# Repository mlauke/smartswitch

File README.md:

# Sonnen SmartSwitch
DIY sonnen battery controller based on ESP8266/ESP32 to drive a 3.3kW heater (Heißwasserspeicher-Einbauheizung) and integrates with the local hot water system.

## Features
- accesses the local hot water system (boiler system) via **LPB** to get the hot water system data - e.g. hot water temparature
- calculate battery capacity and surplus from **solar forecast** to optimize the self consumption
- local web interface to customize system parameters

## UI

## Software / Releases
the software supports ESP8266 and ESP32 modules, which can be build for the appropriate target platform. releases can be found at https://github.com/mlauke/smartswitch/releases/

### Build
Install uv (https://docs.astral.sh/uv/concepts/tools/) and run proceed to source folder
```bash
cd smartswitch.espxx
# run tests
uv run pio test -e native
# run build
uv run pio run -e esp32 -e esp8266
# run check for outdated packages
uv run pio pkg outdated
```

## Hardware
the reference implementation (at my home) uses the following components
- Heater - https://www.austria-email.at/produkte/zubehoer/elektro-einbauheizung/reu-18-33/
- Hot Water Tank - https://www.austria-email.at/produkte/indirekt-beheizte-speicher/standspeicher/standspeicher-hr/hr-160/
- Sonnen Battery https://sonnen.de/stromspeicher/sonnenbatterie-10/
- Boiler System - Siemens RVD250 attached and connected to the ESP controller via the Local Process Bus (LPB)
- ESP8266/ESP32 controller modules
- ArduiBox housing https://www.az-delivery.de/en/products/arduibox-nodemcu-hutschienen-montage-und-anschluss-set
- DIN Rail Power supply +12V
- AC mains Triac cicuit to drive a 1NO Relay
- 1NO Relay (Schütz) https://www.reichelt.de/de/de/shop/produkt/schaltrelais_1_s_230_v_ac_16_a-155592

### Schematics

The schematics and pcb is drawn with KiCad. The pcb uses a special layout which exactly matches the usable part of the ArduiBox's circuit board. KiCad files can be found <a href="kicad/">here.</a>

<p align="center">

</p>

### Housing

<details open align="center">
<summary>Housing</summary>

<!--a href="public/sss_fusebox_big.png">

</details>

### Thoughts
#### Why not using a TRIAC only solution?
Although Triacs have very low Rs_on values in nowadays, they become very hot depending on the load to drive. Using a 3.3kW heater will require a big heatsink as can be seen in the calculation below.

```bash
Pmax = (Tj,max - Tamb,max) / Rth

I = P / U = 3300W / 230 V = 14,35A
Rs_on (BTA25) = 0,16 Ohm
P_loss = U * I = Rs_on * I * I
P_loss = 0,16 Ohm * (14,35 A)²
P_loss = 32,95W

R_max = (T_max - T_env) / P_loss
R_max = (120°C - 40°C) / 33W
R_max = 2,42K/W
R_heatsink = R_max - R_jc = 2,42K/W - 1,7K/W
R_heatsink = 0,7K/W !!!
```

... heatsink with <=0,7K/W makes no sense, because we will waste too much power wasted just for heating the environment and maybe would "blow up" the overall system design in terms of size and housing the components.
therefore i decided to use a triac as switching device for a simple NO1 relais ("Schütz") which in turn will drive the load. the NO1 relais can directly placed next to the arduino case on our din rail.

#### Why not using a SSR?
as mentioned above, a SSR which can drive the 3,3kW load will become very hot if the load is switched on for longer heating periods. too hot to put the SSR together with the ESP controller board on a din rail inside of my houses fuse box.

## Vision
- hardware
  - build a GaN (HEMT) AC Power Converter to dynamically control the "waste" of surplus power based on a bidirection GaN (HEMT) device => https://www.infineon.com/products/power/gallium-nitride/gan-bidirectional-switches/high-voltage-gan-bidirectional-switches e.g. https://www.infineon.com/part/IGLT65R055B2

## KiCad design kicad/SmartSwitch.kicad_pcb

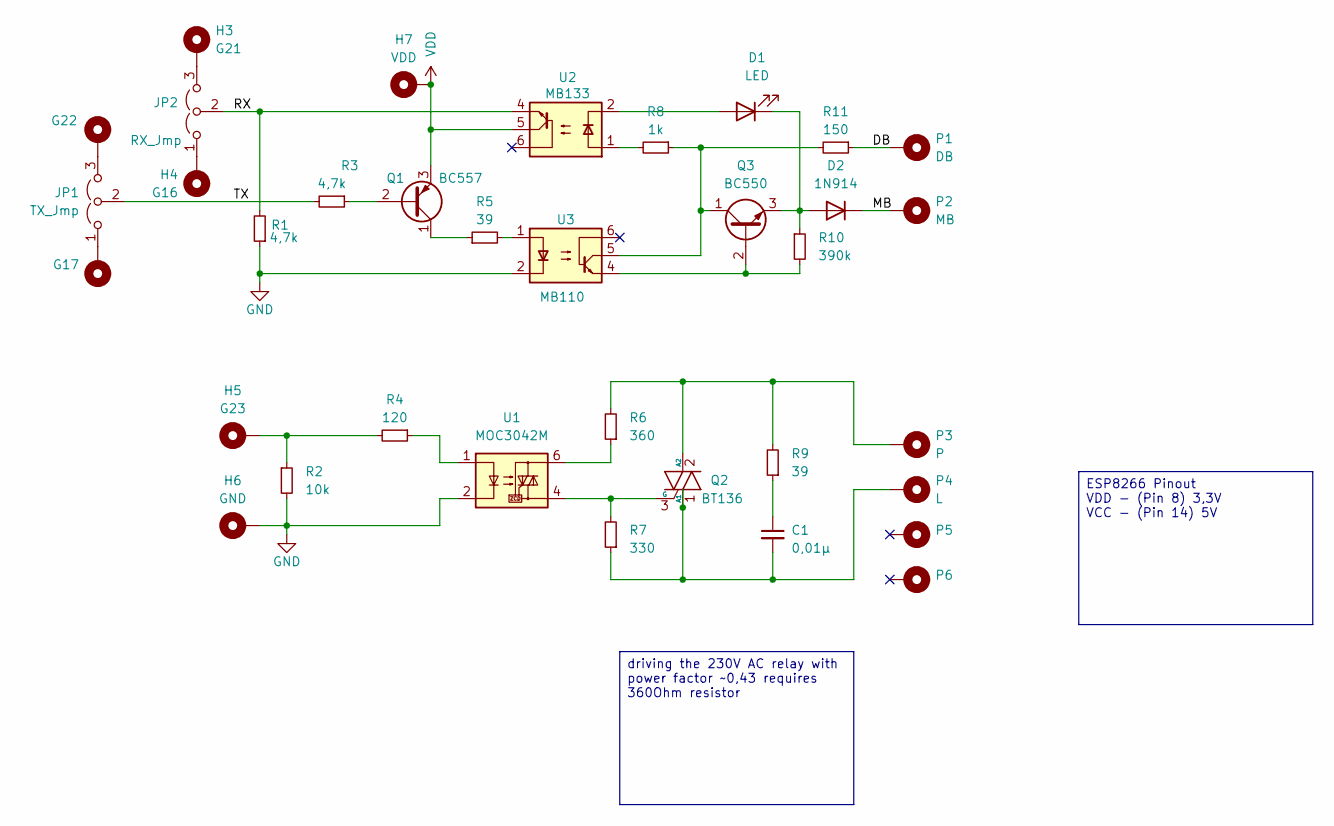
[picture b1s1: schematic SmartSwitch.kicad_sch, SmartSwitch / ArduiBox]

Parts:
C1: 0,01µ; C_Disc_D7.5mm_W2.5mm_P5.00mm
D1: LED; LED_D4.0mm
D2: 1N914; D_DO-35_SOD27_P10.16mm_Horizontal
H1: G22; SolderWire-0.1sqmm_1x01_D0.4mm_OD1mm
H2: G17; SolderWire-0.1sqmm_1x01_D0.4mm_OD1mm
H3: G21; SolderWire-0.1sqmm_1x01_D0.4mm_OD1mm
H4: G16; SolderWire-0.1sqmm_1x01_D0.4mm_OD1mm
H5: G23; SolderWire-0.1sqmm_1x01_D0.4mm_OD1mm
H6: GND; SolderWire-0.1sqmm_1x01_D0.4mm_OD1mm
H7: VDD; SolderWire-0.1sqmm_1x01_D0.4mm_OD1mm
JP1: TX_Jmp; PinHeader_1x03_P2.54mm_Vertical
JP2: RX_Jmp; PinHeader_1x03_P2.54mm_Vertical
P1: DB; SolderWire-0.1sqmm_1x01_D0.4mm_OD1mm
P2: MB; SolderWire-0.1sqmm_1x01_D0.4mm_OD1mm
P3: P; SolderWire-0.1sqmm_1x01_D0.4mm_OD1mm
P4: L; SolderWire-0.1sqmm_1x01_D0.4mm_OD1mm
P5, P6: SolderWire-0.1sqmm_1x01_D0.4mm_OD1mm
Q1: BC557; TO-92_Inline
Q2: BT136; TO-220-3_Vertical
Q3: BC550; TO-92_Inline
R1, R3: 4,7k; R_Axial_DIN0207_L6.3mm_D2.5mm_P10.16mm_Horizontal
R2: 10k; R_Axial_DIN0207_L6.3mm_D2.5mm_P10.16mm_Horizontal
R4: 120; R_Axial_DIN0207_L6.3mm_D2.5mm_P10.16mm_Horizontal
R5, R9: 39; R_Axial_DIN0207_L6.3mm_D2.5mm_P10.16mm_Horizontal
R6: 360; R_Axial_DIN0207_L6.3mm_D2.5mm_P10.16mm_Horizontal
R7: 330; R_Axial_DIN0207_L6.3mm_D2.5mm_P10.16mm_Horizontal
R8: 1k; R_Axial_DIN0207_L6.3mm_D2.5mm_P10.16mm_Horizontal
R10: 390k; R_Axial_DIN0207_L6.3mm_D2.5mm_P10.16mm_Horizontal
R11: 150; R_Axial_DIN0207_L6.3mm_D2.5mm_P10.16mm_Horizontal
U1: MOC3042M; DIP-6_W7.62mm
U2: MB133; DIP-6_W7.62mm
U3: MB110; DIP-6_W7.62mm

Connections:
/DB: P1.1, R11.1
/MB: D2.1 (K), P2.1
/RX: JP2.2 (C), R1.2, U2.4
/TX: JP1.2 (C), R3.2
GND: H6.1, R1.1, R2.2, U1.2, U3.2
unnamed: C1.1, R9.1
unnamed: D1.2 (A), U2.2
unnamed: D1.1 (K), D2.2 (A), Q3.3 (E), R10.1
unnamed: H5.1, R2.1, R4.2
unnamed: H2.1, JP1.1 (A)
unnamed: H1.1, JP1.3 (B)
unnamed: H4.1, JP2.1 (A)
unnamed: H3.1, JP2.3 (B)
unnamed: Q1.2 (B), R3.1
unnamed: Q1.1 (C), R5.1
unnamed: C1.2, P4.1, Q2.1 (A1), R7.1
unnamed: P3.1, Q2.2 (A2), R6.2, R9.2
unnamed: Q2.3 (G), R7.2, U1.4
unnamed: Q3.2 (B), R10.2, U3.4
unnamed: Q3.1 (C), R8.1, R11.2, U3.5
unnamed: R4.1, U1.1
unnamed: R5.2, U3.1
unnamed: R6.1, U1.6
unnamed: R8.2, U2.1
VDD: H7.1, Q1.3 (E), U2.5

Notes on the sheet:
ESP8266 Pinout VDD - (Pin 8) 3,3V VCC - (Pin 14) 5V
driving the 230V AC relay with power factor ~0,43 requires 360Ohm resistor

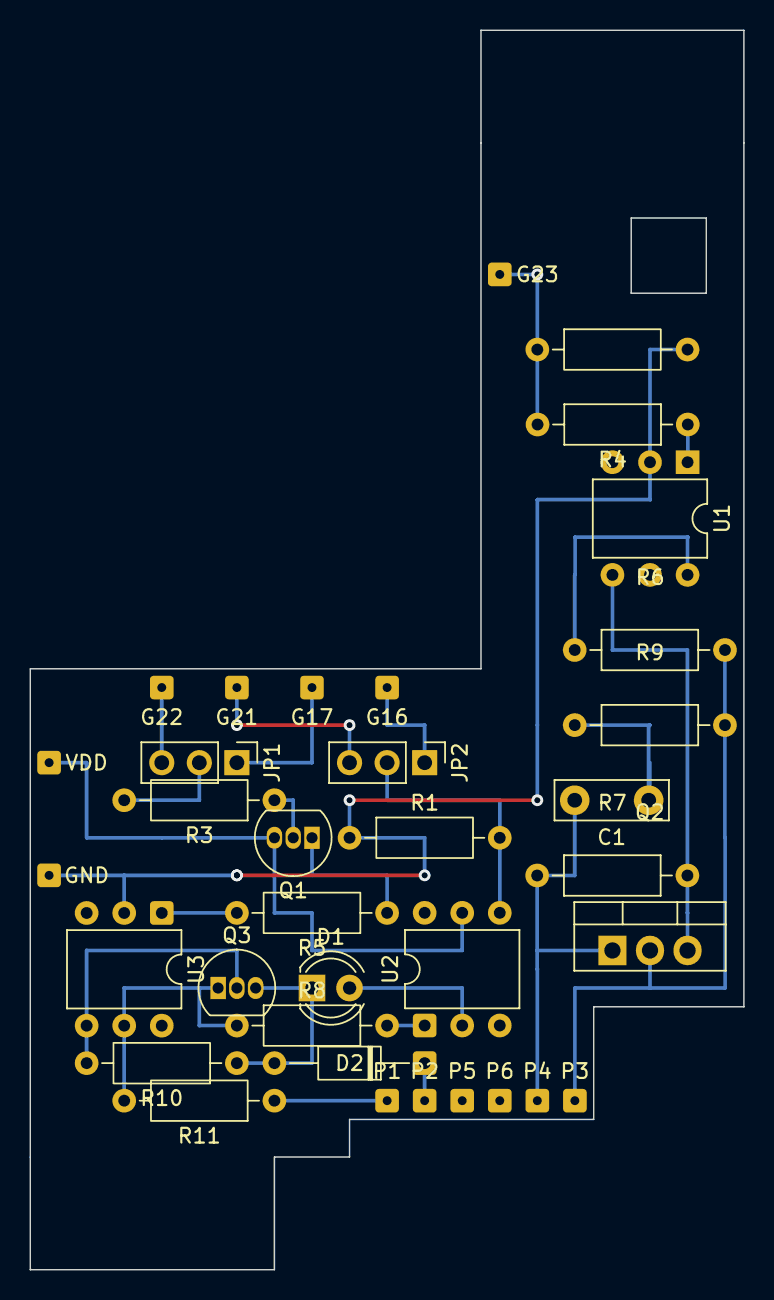
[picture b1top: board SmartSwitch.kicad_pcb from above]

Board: 2 copper layers, 48.3 x 83.8 mm, 35 parts (0 on the bottom side), 25 nets.

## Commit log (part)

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2023-09-06 +initial
2025-02-27 +feat: ota, wifimanager, config
2025-03-03 +feat: webserver, update page
2025-03-04 +fix: build +feat: pv settings
2025-03-04 +fix: release upload
2025-03-04 +fix: http/https support
2025-03-04 +fix asset action +feat: gzip content
2025-03-04 +fix: OTA update
2025-03-04 +fix: release tag update
2025-03-05 +feat: clean code, more ajax
2025-03-05 +fix: NPE, status update
2025-03-05 +fix: status update
2025-03-05 +feat: clean code, hrd
2025-03-15 +feat: impr. form handling +feat: solar forecast
2025-03-17 +feat: pv forecast +fix: js code
2025-03-18 +feat: pv and battery forecast +feat: update ui
2025-03-18 +fix: forecast
2025-03-18 +fix: min capacity update
2025-03-19 +fix: return forecast 0 Wh if no solar forecast available +feature: ui update
2025-03-19 fix: switch off if grid purchase is below threshold
2025-03-19 +fix: grid feed in logic
2025-03-19 +fix: gzip +fix: var names, clean code
2025-03-19 +fix: git update
2025-03-19 +fix update handling
2025-03-19 +fix: status field
2025-03-19 +fix: warning, adjust flash size
2025-03-20 +fix: release_tag
2025-03-20 +fix: clean code
2025-03-20 +fix: gzip compression, encoding
2025-03-20 +feat: ux/ui update, css file +feat: impr. forecast
2025-03-20 +fix: include
2025-03-20 +fix: cache control
2025-03-20 +fix: switch off on data error
2025-03-20 +fix: js retry on error
2025-03-20 +feat: enable on prod > load and cap > 80
2025-03-20 +feat: collect events
2025-03-20 +feat: change hostname
2025-03-20 +feat: restart, reset
2025-03-21 +feat: event log +fix: flicker, use penalty counter for inverter latency
2025-03-21 +fix: latency cnt
2025-03-21 +fix: dark mode event log style
2025-03-25 +feat: layout update +feat: impr. event / error handling +feat: honor discharge not allowed state +feat: impr. update interval +fix: forecast calculation +fix: added panel declination +fix: inverter 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
2025-03-25 +fix: ui and error message +feat: impr. forecast calculation
2025-03-25 +feat: local time conversion +fix: inverter latency
2025-03-25 +fix: event log timestamp handling +feat: localtime on server events
2025-03-25 +feat: clean code, incr. solar forecast update interval
2025-03-25 +feat: favicon
2025-03-25 +fix: path
2025-03-25 +fix: latency count +feat: delay update on error
2025-03-25 +feat: switch on hysterese
2025-03-28 +fix: forecast min/max with hysterese
2025-03-28 +fix: mbusino lib
2025-03-28 +fix: latency count flicker +fix: use local ts in msg
2025-03-28 +fix: disabled if cons > max inverter power
2025-03-28 +feat: ux/ui battery charge/discharge
2025-03-28 +fix: prod mode
2025-03-29 +fix: consumption if switched from on/auto mode +feat: update location from pv data
2025-03-30 +feat: dev mode and solar forecast +feat: use cfg grid min, default 100W
2025-03-31 +fix: capacity update +feat: impr. ui
2025-03-31 +feat: fit to page
2025-04-02 fix: switch on if bat cap > bat_cap min and surplus > load/2w fix: min capacity calculation "flicker" => use rounded avg
2025-04-02 +feat: enable watchdog
2025-04-05 +feat: doc
2025-04-06 +fix: use D7 for SSR +feat: layout update
2025-04-15 +feat: integrate boiler via LPB
2025-04-15 +fix: check client connect during update
2025-05-14 +fix: NPE in update handling and webserver client +feat: impr. UI, add boiler data
2025-05-14 +fix: small layout changes
2025-05-15 +fix: dev mode solarforecast +fix: layout
2025-07-06 +feat: on/off upon boilder data +feat: clean code, impr. boilder api
2025-07-07 +feat: ui update +feat: device detect with retry
2025-07-07 +fix: wifi manager handling
2025-07-10 +feat: esp32 support +feat: clean code
2025-07-10 feat: +initial
2025-07-10 +fix: buildsys
2025-07-10 +fix: build esp8266 binary
2025-07-10 +fix: compress, upload target plattform
2025-07-13 +feat: more verbose, display constraint id in log +fix: runtime error with OTA
2025-07-13 +fix: skipped update will return last result
2025-07-13 +fix: enable ota begin
2025-07-14 +feat: update layout/responsive design +feat: more verbose, event with id
2025-07-24 +feat: migrate toolchain to vscode and PIO
2025-07-24 +fix: build path firmware binaries
2025-07-27 +fix: workaround for esp32 OTA, can only deal with raw file (not gzip) +fix: various OTA update issues +fix: LPB retry and device handling
2025-07-28 +fix: asset name
2025-08-07 +feat: impr. wifi reconnect +feat: impr. ui update, rm handleData call +fix: esp32/esp8266 built in led low/high issue
2025-08-24 +feat: constraint/event message +feat: impr. ui
2025-08-24 +feat: impr. init, clean code
2025-08-24 +feat: more verbose on OTA update
2025-09-02 +feat: impr. OTA with filter json
2025-09-02 +feat: events
2025-09-13 +fix: fix event log +fix: hysteresis +feat: improve log message +feat: update doc
2025-09-14 +fix: low charge state detection
2025-09-18 +fix: load calibrate/update +fix: config data update handling
2025-09-21 +feat: start time +fix: impr. hysteresis
2025-09-21 +feat: load calibration
2025-09-21 +fix: calibrate
2025-09-21 +fix: load calibration
2025-09-22 +fix: impr. calibration calculation
2025-09-22 +fix: calibrate, use system data during switch on/off, more delay after toggle
2025-09-22 +fix: clean code, calibrate exactly
2025-09-23 +feat: impr. ui, asyn calibrate handling
2025-11-12 +fix: hysteresis in battery target +feat: clean code, unit tests +feat: impr. ux/ui
2025-11-13 +impr: esp8266 reduce heap, use flash string literals +fix: OTA handling
2025-11-14 +fix: double confirm in ui +impr: debug output handling +feat: use timezone offset from battery data
2025-12-18 +fix: revision ota, espXX shared code +fix: layout ux/ui alignment +fix: http client handling +feat: enhance lpp init logic
2025-12-18 +fix: partition +fix: ota update and stream handling
2025-12-18 +fix: initial flashfs init and format +fix: hostname update
2025-12-18 +fix: log message buffer
2025-12-18 +feat: update message
2025-12-18 +feat: impr. ota status page
2025-12-19 +fix: esp8266 ota workaround
2025-12-19 +fix: esp8266 http workaround
2025-12-19 +fix: patch buggy esp8266 ota
2025-12-22 +fix: round up load during calibrate
2025-12-22 +fix: enable tests
2025-12-28 +fix: forecast url dec, az interchanged +fix: always check overload constraint +feat: clean code
2026-01-05 +fix: constraint msg +feat: 3% from calibrated load
2026-01-14 +feat: cycle count +fix: workaround the full charge request (maintenance) +fix: battery data update every 4 hours +fix: clean code, variable namings
2026-01-14 +feat: impr. calibrate, use median +fix: load power 0 error +fix: security issue with api token
2026-01-16 +fix: inverter latency count
2026-01-18 +feat: battery usable capacity percentage +fix: clean code, message format
2026-01-18 +fix: test, logic code
2026-01-18 +feat: decouple code for testing purpose
2026-01-18 +fix: percentage, test code
2026-01-18 +fix: uint support
2026-01-18 +fix: compatibility to test
2026-01-19 +feat: clean code
2026-01-19 +feat: temperature with decimal precision 2
2026-01-20 +fix: surplus vs. battery goal flicker
2026-01-20 +feat: refactoring on/off logic, more readable
2026-01-21 +fix: cons under load
2026-01-21 +feat: impr. RAM
2026-01-21 +fix: esp32 target
2026-01-21 +feat: more tests, clean code
2026-01-27 +fix: seg fault +feat: more verbose log message
2026-02-02 +fix: flicker, switch off on system overload only
2026-02-02 +fix: load hysteresis, adjust tests
2026-02-03 +fix: fmt for int value
2026-02-03 +feat: assert message
2026-02-03 +fix: surplus waste deactivated until valid state is available
2026-02-06 +fix: esp32 hw serial lpb support
2026-02-11 +fix: npe +fix: name of lpb debug define
2026-02-16 +fix: more hysteresis
2026-02-17 +feat: meta data
2026-02-17 +feat: meta data style
2026-03-02 +fix: full charge request json +feat: impr. forecast with weight +feat: enable load if wasted surplus is greater then load +feat: fetch sonnen, use json filter +feat: impr. lpb findline, get rid of f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
2026-03-03 +feat: more aggressive load if max will be reached
2026-03-03 +fix: break early
2026-03-04 +fix: forecast and trend indicator
2026-03-04 +fix: enable load on positive trend with hysteresis
2026-03-04 +fix: clean code, naming +fix: pull down for reliable state after reset
2026-03-05 +feat: more verbose +fix: hardening battery capacity trend
2026-03-05 +fix: more hysteresis below min capacity
2026-03-05 +feat: serial id
2026-03-05 +feat: disable debug
2026-03-06 +feat: device details
2026-03-08 +feat: incr. stable count, more tests
2026-03-08 +feat: do switch control although no pv forecast data available - e-g- surplus waste
2026-03-08 +fix: compile :/
2026-03-08 +feat: pipeline with uv
2026-03-08 +fix: python version
2026-03-08 +fix: pio requires pip
2026-03-08 +fix: clean dir
2026-03-08 +fix: pipe in run
2026-03-08 +fix: use WORKDIR var
2026-03-08 +feat: update readme
2026-03-08 +feat: skip desired state if mode not set to auto
2026-03-08 +feat: docu, kicad
2026-03-08 +fix: desired state
2026-03-08 +fix: low capacity switch off
2026-03-08 +fix: 20min hysteresis
2026-03-13 +fix: final capacity below min wont switch on
2026-03-17 +fix: balanced below min usoc +fix: clean kicad pcb
2026-03-18 fix: calibrate button/spinner layout bug
2026-03-18 +fix: label layout
2026-03-18 +feat: more verbose message
2026-03-20 +feat: invalid data error cause +fix: ux/ui overlay
2026-03-20 +fix: event log buffer
2026-03-20 +fix: calculate battery capacity with consumption in wh
2026-03-20 +fix: formatting, more tests
2026-03-23 +fix: log overlay layout +fix: clean code
2026-03-23 +fix: impr. overlay
2026-03-23 +fix: overlay empty log
2026-03-23 +fix: clean code, pstr
2026-03-25 +fix: ramining hours label
2026-03-29 fix: correct critical bugs found in code review
    - LPB.cpp: fix assignment-instead-of-comparison (type = 0x14 → type == 0x14)
    in response matching condition
    - LPB.cpp: fix NaN temperature check (== NAN → isnan()) — IEEE 754 makes
    == NAN always false, causing failed reads to silently propagate
    - Logic.h: fix off-by-one in findPvForecastData loop (i <= → i <
    SOLAR_FORECAST_HOURS) preventing out-of-bounds array access
2026-03-30 +feat: consumption stats bar chart overlay with y/x axis
    - Add cons_stats_Wh[7][24] EMA tracking (α=0.1) per weekday×hour in Logic.h
    - Persist stats to flash hourly (no version bump) via saveConfig(false)
    - Reset stats on location change
    - Use per-hour stats in predictBatteryCapacityState() with fallback to cons_W_norm
    - Expose cons_stats nested array in /api/data JSON response
    - Frontend: bar chart overlay triggered from Consumption row (Stats link)
2026-03-30 fix: replace per-tick EMA with true hourly mean for consumption stats
    EMA applied every 2s caused the stored value to reflect only the last
    ~20 seconds of the hour rather than a real hourly average. Fix
    accumulates samples within the hour (sum + count), computes the
    arithmetic mean on hour rollover, then blends it into the historical
    slot via cross-week EMA α=0.1.
    Adds cons_sum_W / cons_count transient fields to SystemState.
2026-03-30 +feat: max cap Wh to battery +feat: bump version also on stats update
2026-03-31 +feat: expire date to certs.h +fix: statistics bar title
2026-03-31 +feat: update
2026-03-31 +feat: also display current hour mean
2026-03-31 +fix: avg consumption
2026-03-31 +feat: solar forecast bars in stats overlay
2026-04-01 +fix: hourly stats become invalid if battery is not reachable, sanity check added
2026-04-01 +fix: cons_avg override from battery +fix: do not reset cons average on hourly rollover
2026-04-02 +fix: ui, consider consumption avg. max value in statistics
2026-04-02 +feat: daily consumption and pv forecast to statistics
2026-04-09 +feat: impr. ui stats, determine max value from forecast and consumption to draw y axis +fix: bug: flicker when SoC 0% +fix: bug: flicker when consumption without load is very low
2026-05-05 +feat: upgrade dependencies +feat: log message +feat: nginx proxy deamon
2026-05-11 +feat: reset statistic on location update
2026-06-13 +fix: switch on if waste exceeds load and battery will full charge anyway, although usoc is 0
2026-06-15 +fix: battery fully charged or will full charge (max) but no surplus is available
